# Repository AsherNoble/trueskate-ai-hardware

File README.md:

# trueskate-ai-hardware

Hand-control layer for TrueSkate-AI. Slots in where WebDriverAgent does for
the phones: the agent sends touch gestures, this repo makes a robotic finger
perform them.

Time-critical control (FOC, trajectory execution, safety) runs on a Teensy
4.1. The host sends commands and reads state back; it never runs a control
loop.

## Structure

```
firmware/   PlatformIO project, board teensy41
  src/        controller firmware, one Axis per finger
  bringup/    bench sketches kept for the record, unchanged
host/       Python package (uv), touch API + motor clients
  src/        trueskate_ai_hardware
  config/     hand.yaml
  tests/      mock-path tests, no hardware needed
docs/       wiring, pin map, bring-up notes, protocol draft
pcb/        through-hole six-axis carrier, KiCad source and review package
```

## Build the firmware

```sh
cd firmware && pio run
```

Does not flash. Add `-t upload` with the board connected.

## Run the host tests

```sh
cd host && uv sync --extra dev && uv run pytest
```

## Status

Firmware drives one axis and builds. The host is a skeleton: the touch API
mirrors the interface but does not move anything, and the serial protocol in
`docs/protocol.md` is a draft. `MockMotorClient` works with no hardware.

Start with [docs/bringup.md](docs/bringup.md) for what the bench has proved.

The [six-axis carrier review package](pcb/README.md) is a separate hardware
design, not yet released for fabrication. Its current edge layout uses six JLC-assembled JST connectors, hand-soldered THT parts,
and a hardware kill circuit. See [layout changes and outstanding checks](docs/pcb/edge-layout.md); start with the
[one-page net guide](docs/pcb/nets.md). Firmware still needs migration from the
one-axis bench pin assignments before use with this carrier.

## Licence

MIT. `orca_core` (MIT, ORCA) was studied as a reference for the motor-client
and serial-framing patterns; no code was copied.

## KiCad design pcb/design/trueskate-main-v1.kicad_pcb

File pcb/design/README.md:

# Current KiCad design

Open [trueskate-main-v1.kicad_pro](trueskate-main-v1.kicad_pro) in KiCad 10.
The project opens the PCB and its hierarchical schematic sheets. The local
symbol/footprint libraries and their tables live beside the project, so KiCad's
`${KIPRJMOD}` references remain relative and portable.

`data/` contains the declarative axis/pin mapping, nominal stackup, circuit data,
manual route records and placement baseline used by the scripts. `routing/`
contains the checked-in signal-routing session. See [tool commands](../scripts/README.md)
before rebuilding: regeneration overwrites the native design.

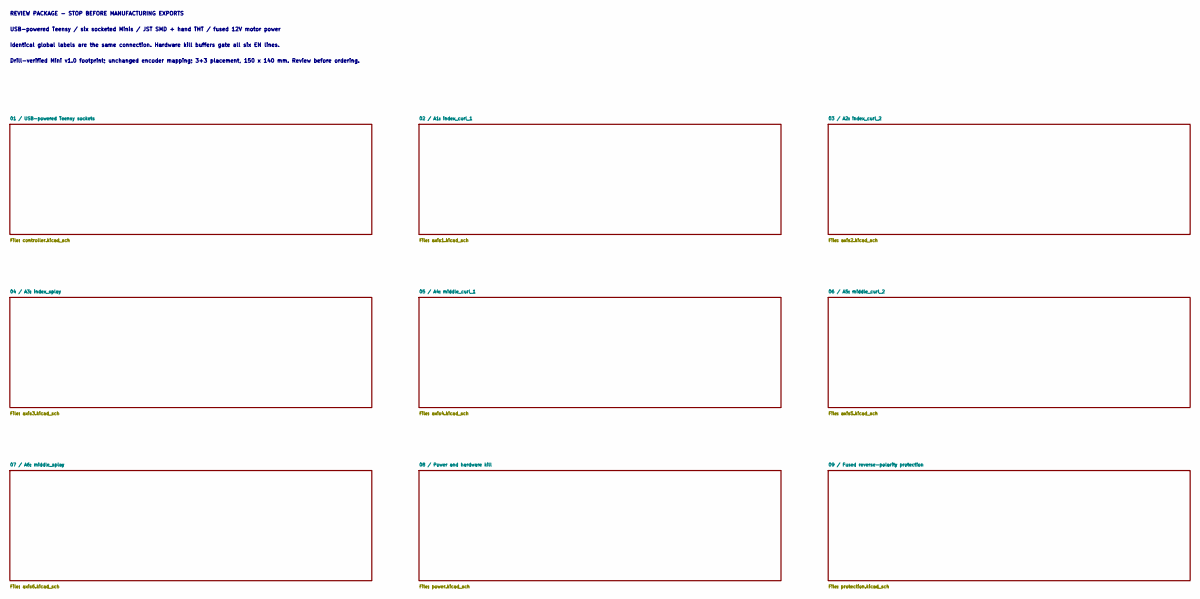
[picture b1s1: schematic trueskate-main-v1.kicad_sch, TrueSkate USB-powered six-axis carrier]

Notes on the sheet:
REVIEW PACKAGE - STOP BEFORE MANUFACTURING EXPORTS
USB-powered Teensy / six socketed Minis / JST SMD + hand THT / fused 12V motor power
Identical global labels are the same connection. Hardware kill buffers gate all six EN lines.
Drill-verified Mini v1.0 footprint; unchanged encoder mapping; 3+3 placement, 150 x 140 mm. Review before ordering.

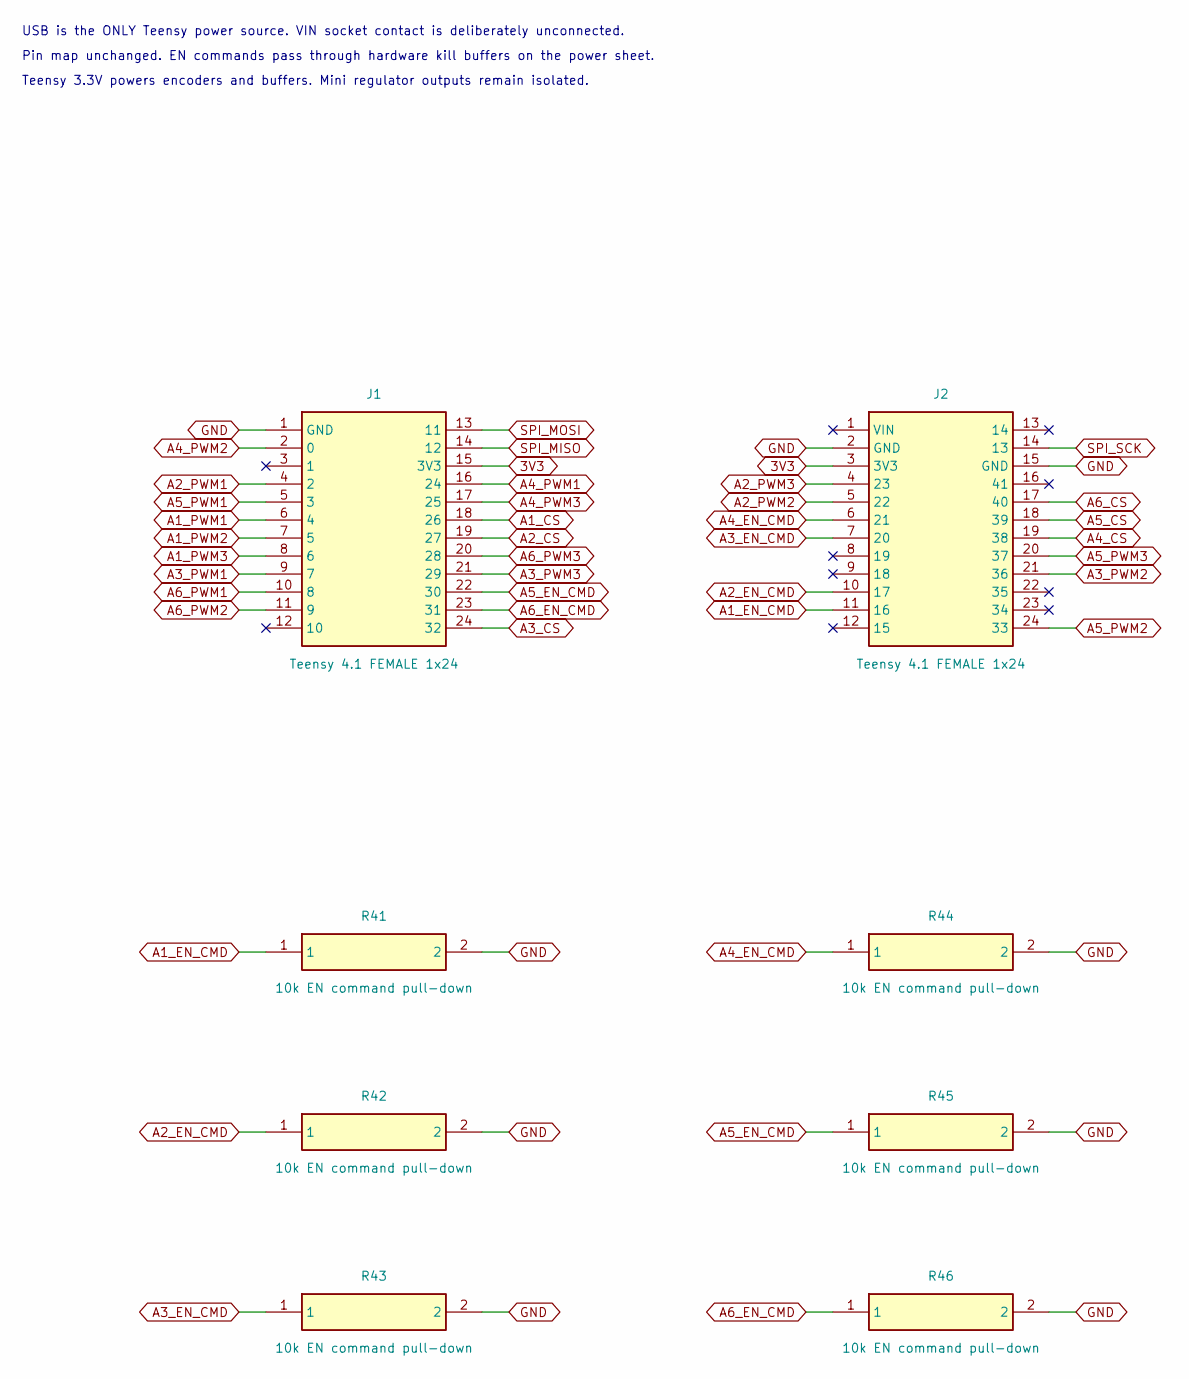
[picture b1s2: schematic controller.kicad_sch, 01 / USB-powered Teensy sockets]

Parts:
J1, J2: Teensy 4.1 FEMALE 1x24; Edge_PinSocket_1x24_P2.54mm_Vertical
R41, R42, R43, R44, R45, R46: 10k EN command pull-down; Edge_R_Axial_DIN0207_L6.3mm_D2.5mm_P7.62mm_Horizontal

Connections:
3V3: J1.15 (3V3), J2.3 (3V3); also elsewhere on the board
A1_CS: J1.18 (26); also elsewhere on the board
A1_EN_CMD: J2.11 (16), R41.1; also elsewhere on the board
A1_PWM1: J1.6 (4); also elsewhere on the board
A1_PWM2: J1.7 (5); also elsewhere on the board
A1_PWM3: J1.8 (6); also elsewhere on the board
A2_CS: J1.19 (27); also elsewhere on the board
A2_EN_CMD: J2.10 (17), R42.1; also elsewhere on the board
A2_PWM1: J1.4 (2); also elsewhere on the board
A2_PWM2: J2.5 (22); also elsewhere on the board
A2_PWM3: J2.4 (23); also elsewhere on the board
A3_CS: J1.24 (32); also elsewhere on the board
A3_EN_CMD: J2.7 (20), R43.1; also elsewhere on the board
A3_PWM1: J1.9 (7); also elsewhere on the board
A3_PWM2: J2.21 (36); also elsewhere on the board
A3_PWM3: J1.21 (29); also elsewhere on the board
A4_CS: J2.19 (38); also elsewhere on the board
A4_EN_CMD: J2.6 (21), R44.1; also elsewhere on the board
A4_PWM1: J1.16 (24); also elsewhere on the board
A4_PWM2: J1.2 (0); also elsewhere on the board
A4_PWM3: J1.17 (25); also elsewhere on the board
A5_CS: J2.18 (39); also elsewhere on the board
A5_EN_CMD: J1.22 (30), R45.1; also elsewhere on the board
A5_PWM1: J1.5 (3); also elsewhere on the board
A5_PWM2: J2.24 (33); also elsewhere on the board
A5_PWM3: J2.20 (37); also elsewhere on the board
A6_CS: J2.17 (40); also elsewhere on the board
A6_EN_CMD: J1.23 (31), R46.1; also elsewhere on the board
A6_PWM1: J1.10 (8); also elsewhere on the board
A6_PWM2: J1.11 (9); also elsewhere on the board
A6_PWM3: J1.20 (28); also elsewhere on the board
GND: J1.1 (GND), J2.2 (GND), J2.15 (GND), R41.2, R42.2, R43.2, R44.2, R45.2, R46.2; also elsewhere on the board
SPI_MISO: J1.14 (12); also elsewhere on the board
SPI_MOSI: J1.13 (11); also elsewhere on the board
SPI_SCK: J2.14 (13); also elsewhere on the board

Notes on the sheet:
USB is the ONLY Teensy power source. VIN socket contact is deliberately unconnected.
Pin map unchanged. EN commands pass through hardware kill buffers on the power sheet.
Teensy 3.3V powers encoders and buffers. Mini regulator outputs remain isolated.

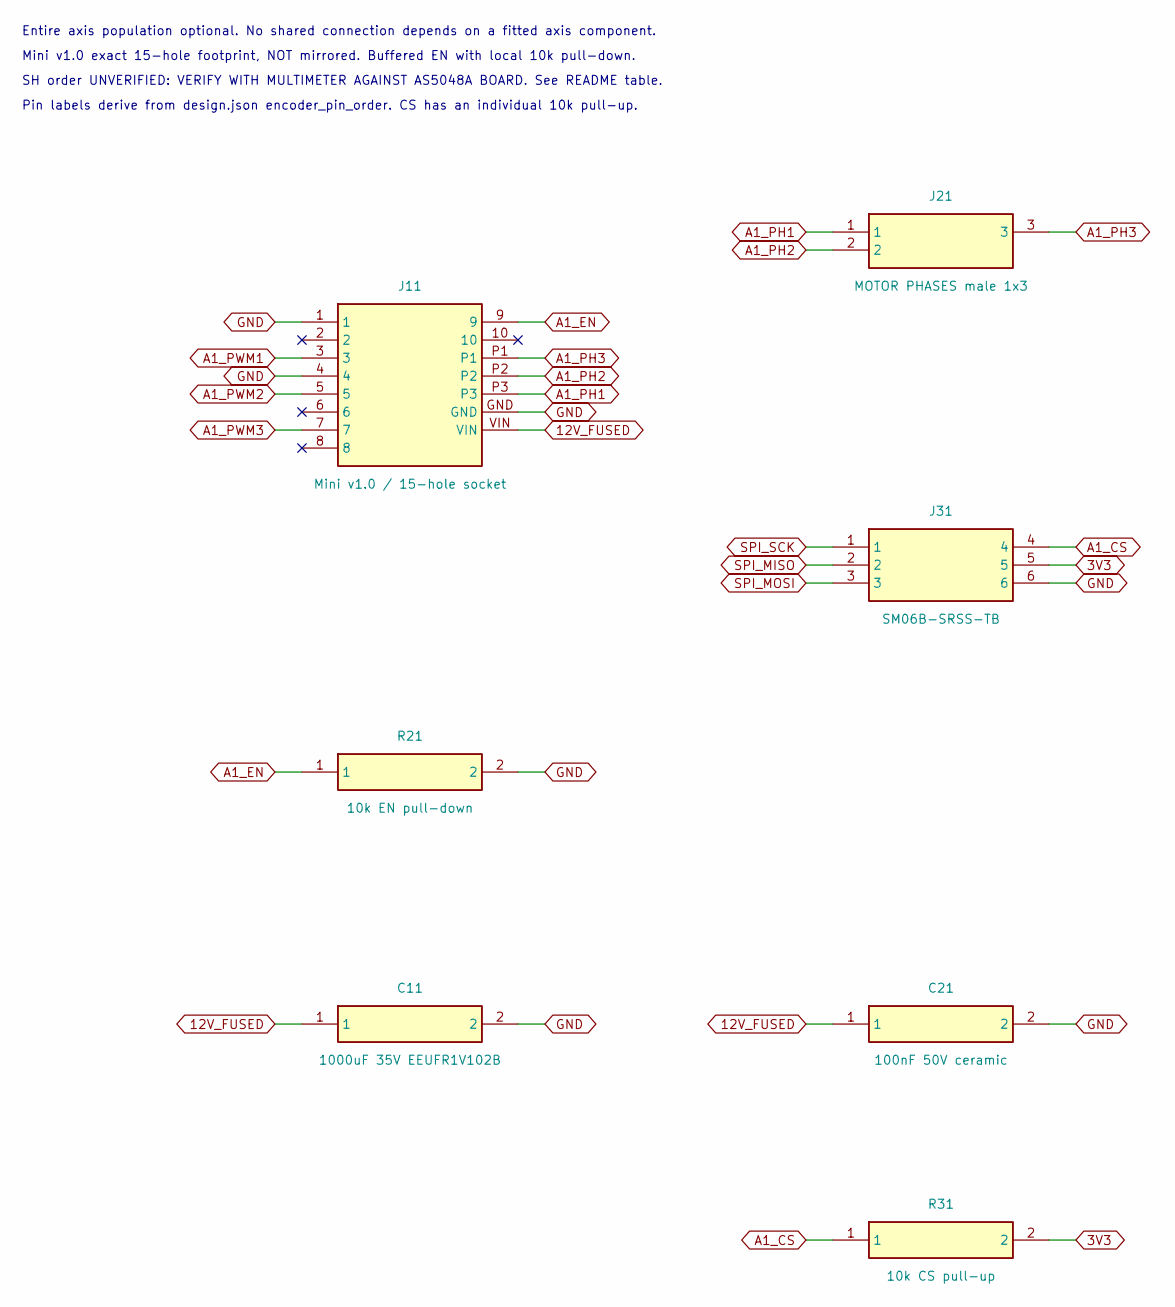
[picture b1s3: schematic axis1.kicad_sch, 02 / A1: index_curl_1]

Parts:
C11: 1000uF 35V EEUFR1V102B; Edge_CP_Radial_D12.5mm_P5.00mm
C21: 100nF 50V ceramic; Edge_C_Disc_D5.0mm_W2.5mm_P5.00mm
J11: Mini v1.0 / 15-hole socket; SimpleFOC_Mini_v1.0
J21: MOTOR PHASES male 1x3; Edge_PinHeader_1x03_P2.54mm_Vertical
J31: SM06B-SRSS-TB; Edge_JST_SH_SM06B-SRSS-TB_1x06-1MP_P1.00mm_Horizontal
R21: 10k EN pull-down; Edge_R_Axial_DIN0207_L6.3mm_D2.5mm_P7.62mm_Horizontal
R31: 10k CS pull-up; Edge_R_Axial_DIN0207_L6.3mm_D2.5mm_P7.62mm_Horizontal

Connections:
3V3: J31.5, R31.2; also elsewhere on the board
12V_FUSED: C11.1, C21.1, J11.VIN; also elsewhere on the board
A1_CS: J31.4, R31.1; also elsewhere on the board
A1_EN: J11.9, R21.1; also elsewhere on the board
A1_PH1: J11.P3, J21.1
A1_PH2: J11.P2, J21.2
A1_PH3: J11.P1, J21.3
A1_PWM1: J11.3; also elsewhere on the board
A1_PWM2: J11.5; also elsewhere on the board
A1_PWM3: J11.7; also elsewhere on the board
GND: C11.2, C21.2, J11.1, J11.4, J11.GND, J31.6, R21.2; also elsewhere on the board
SPI_MISO: J31.2; also elsewhere on the board
SPI_MOSI: J31.3; also elsewhere on the board
SPI_SCK: J31.1; also elsewhere on the board

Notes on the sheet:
Entire axis population optional. No shared connection depends on a fitted axis component.
Mini v1.0 exact 15-hole footprint, NOT mirrored. Buffered EN with local 10k pull-down.
SH order UNVERIFIED: VERIFY WITH MULTIMETER AGAINST AS5048A BOARD. See README table.
Pin labels derive from design.json encoder_pin_order. CS has an individual 10k pull-up.

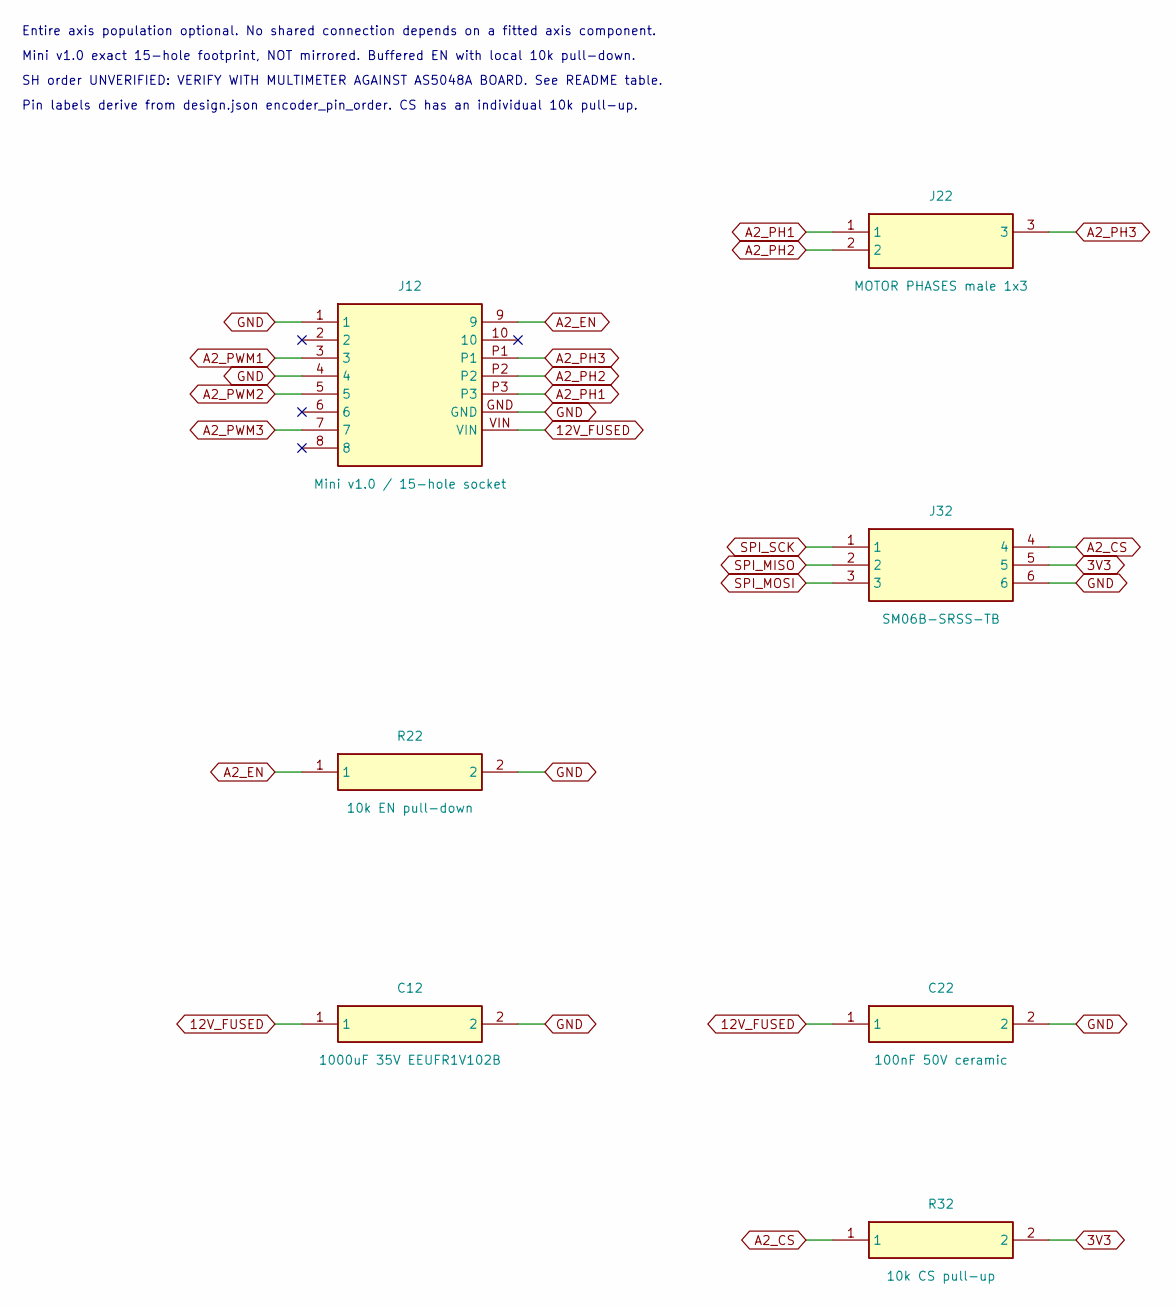
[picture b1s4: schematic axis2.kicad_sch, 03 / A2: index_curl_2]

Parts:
C12: 1000uF 35V EEUFR1V102B; Edge_CP_Radial_D12.5mm_P5.00mm
C22: 100nF 50V ceramic; Edge_C_Disc_D5.0mm_W2.5mm_P5.00mm
J12: Mini v1.0 / 15-hole socket; SimpleFOC_Mini_v1.0
J22: MOTOR PHASES male 1x3; Edge_PinHeader_1x03_P2.54mm_Vertical
J32: SM06B-SRSS-TB; Edge_JST_SH_SM06B-SRSS-TB_1x06-1MP_P1.00mm_Horizontal
R22: 10k EN pull-down; Edge_R_Axial_DIN0207_L6.3mm_D2.5mm_P7.62mm_Horizontal
R32: 10k CS pull-up; Edge_R_Axial_DIN0207_L6.3mm_D2.5mm_P7.62mm_Horizontal

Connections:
3V3: J32.5, R32.2; also elsewhere on the board
12V_FUSED: C12.1, C22.1, J12.VIN; also elsewhere on the board
A2_CS: J32.4, R32.1; also elsewhere on the board
A2_EN: J12.9, R22.1; also elsewhere on the board
A2_PH1: J12.P3, J22.1
A2_PH2: J12.P2, J22.2
A2_PH3: J12.P1, J22.3
A2_PWM1: J12.3; also elsewhere on the board
A2_PWM2: J12.5; also elsewhere on the board
A2_PWM3: J12.7; also elsewhere on the board
GND: C12.2, C22.2, J12.1, J12.4, J12.GND, J32.6, R22.2; also elsewhere on the board
SPI_MISO: J32.2; also elsewhere on the board
SPI_MOSI: J32.3; also elsewhere on the board
SPI_SCK: J32.1; also elsewhere on the board

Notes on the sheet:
Entire axis population optional. No shared connection depends on a fitted axis component.
Mini v1.0 exact 15-hole footprint, NOT mirrored. Buffered EN with local 10k pull-down.
SH order UNVERIFIED: VERIFY WITH MULTIMETER AGAINST AS5048A BOARD. See README table.
Pin labels derive from design.json encoder_pin_order. CS has an individual 10k pull-up.

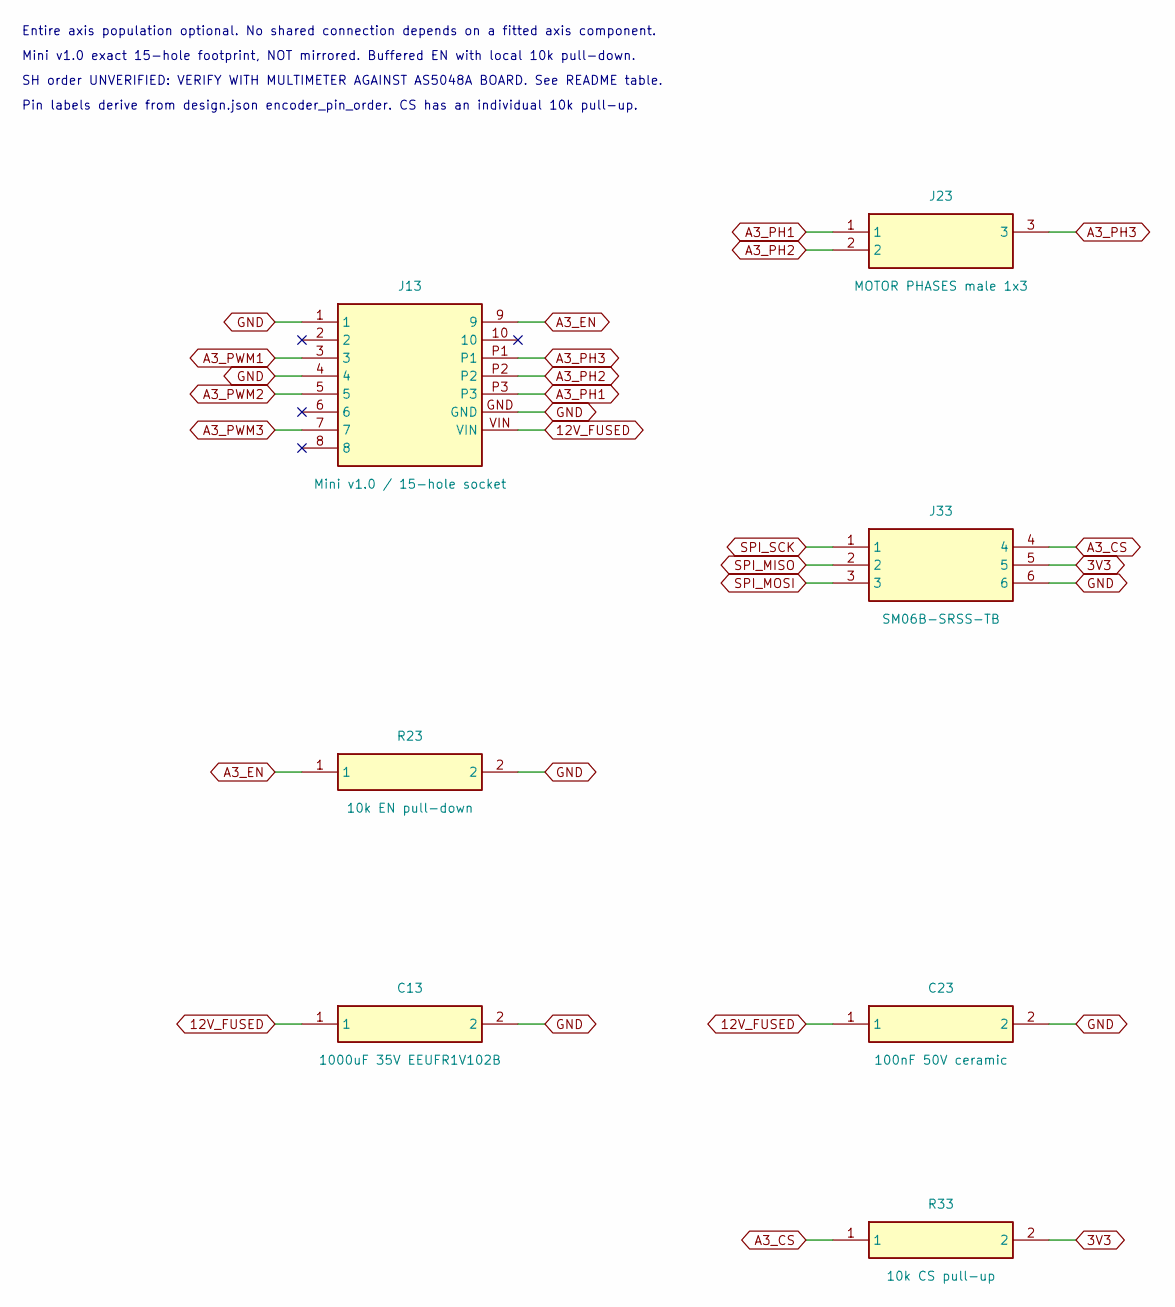
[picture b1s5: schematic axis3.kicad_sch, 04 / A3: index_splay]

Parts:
C13: 1000uF 35V EEUFR1V102B; Edge_CP_Radial_D12.5mm_P5.00mm
C23: 100nF 50V ceramic; Edge_C_Disc_D5.0mm_W2.5mm_P5.00mm
J13: Mini v1.0 / 15-hole socket; SimpleFOC_Mini_v1.0
J23: MOTOR PHASES male 1x3; Edge_PinHeader_1x03_P2.54mm_Vertical
J33: SM06B-SRSS-TB; Edge_JST_SH_SM06B-SRSS-TB_1x06-1MP_P1.00mm_Horizontal
R23: 10k EN pull-down; Edge_R_Axial_DIN0207_L6.3mm_D2.5mm_P7.62mm_Horizontal
R33: 10k CS pull-up; Edge_R_Axial_DIN0207_L6.3mm_D2.5mm_P7.62mm_Horizontal

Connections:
3V3: J33.5, R33.2; also elsewhere on the board
12V_FUSED: C13.1, C23.1, J13.VIN; also elsewhere on the board
A3_CS: J33.4, R33.1; also elsewhere on the board
A3_EN: J13.9, R23.1; also elsewhere on the board
A3_PH1: J13.P3, J23.1
A3_PH2: J13.P2, J23.2
A3_PH3: J13.P1, J23.3
A3_PWM1: J13.3; also elsewhere on the board
A3_PWM2: J13.5; also elsewhere on the board
A3_PWM3: J13.7; also elsewhere on the board
GND: C13.2, C23.2, J13.1, J13.4, J13.GND, J33.6, R23.2; also elsewhere on the board
SPI_MISO: J33.2; also elsewhere on the board
SPI_MOSI: J33.3; also elsewhere on the board
SPI_SCK: J33.1; also elsewhere on the board

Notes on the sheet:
Entire axis population optional. No shared connection depends on a fitted axis component.
Mini v1.0 exact 15-hole footprint, NOT mirrored. Buffered EN with local 10k pull-down.
SH order UNVERIFIED: VERIFY WITH MULTIMETER AGAINST AS5048A BOARD. See README table.
Pin labels derive from design.json encoder_pin_order. CS has an individual 10k pull-up.

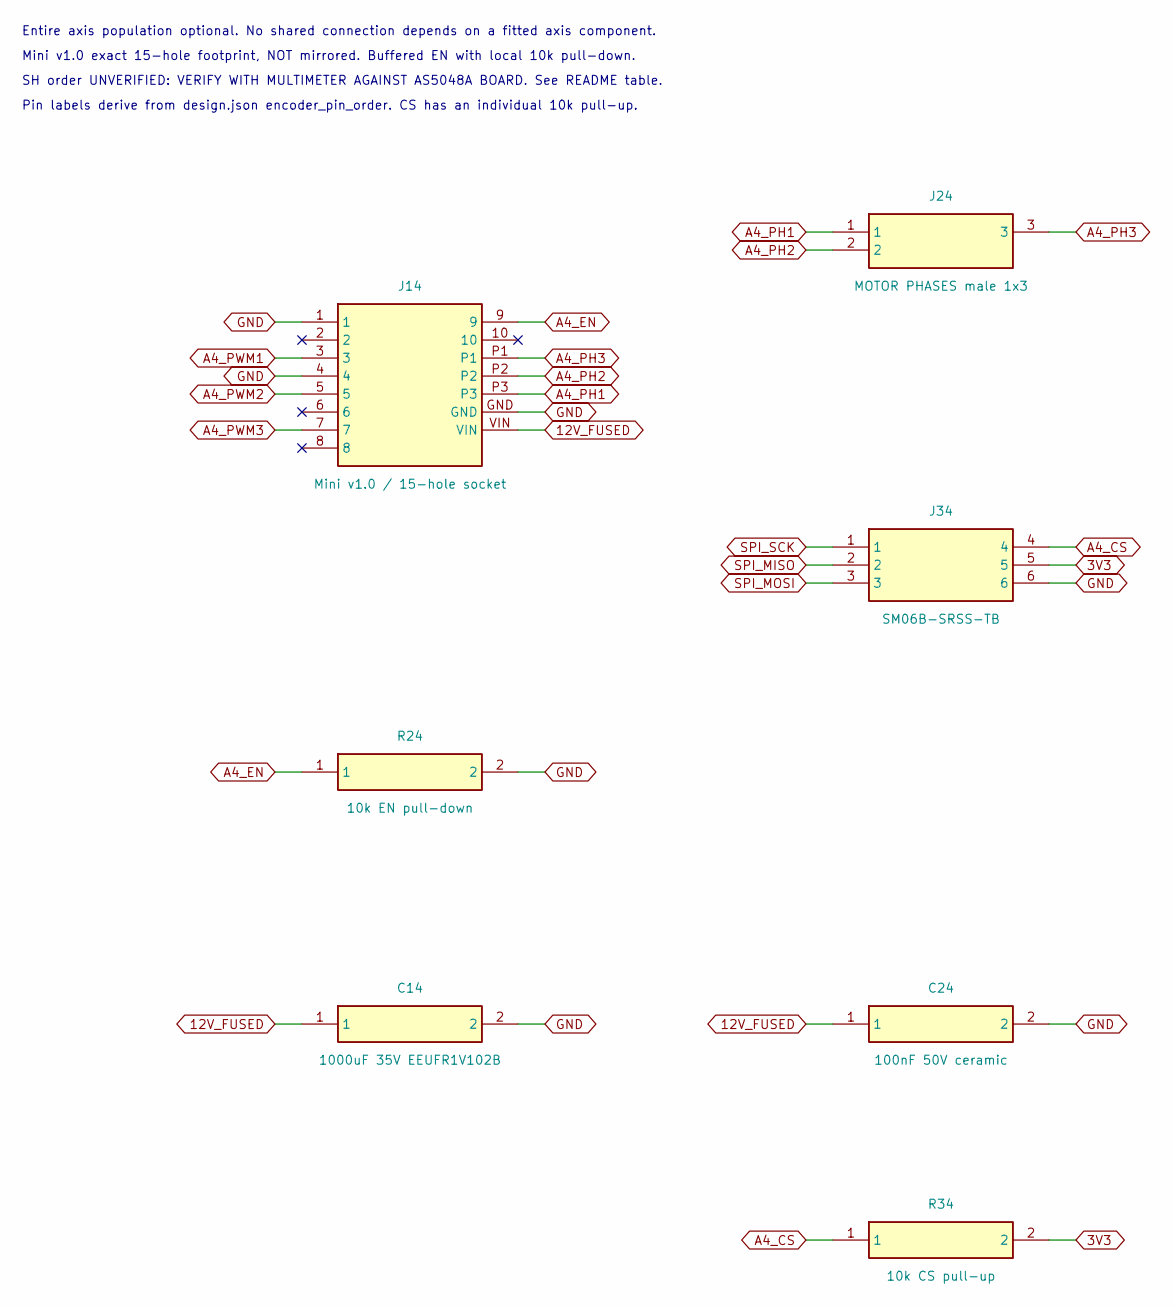
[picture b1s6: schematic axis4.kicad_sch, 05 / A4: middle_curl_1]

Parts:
C14: 1000uF 35V EEUFR1V102B; Edge_CP_Radial_D12.5mm_P5.00mm
C24: 100nF 50V ceramic; Edge_C_Disc_D5.0mm_W2.5mm_P5.00mm
J14: Mini v1.0 / 15-hole socket; SimpleFOC_Mini_v1.0
J24: MOTOR PHASES male 1x3; Edge_PinHeader_1x03_P2.54mm_Vertical
J34: SM06B-SRSS-TB; Edge_JST_SH_SM06B-SRSS-TB_1x06-1MP_P1.00mm_Horizontal
R24: 10k EN pull-down; Edge_R_Axial_DIN0207_L6.3mm_D2.5mm_P7.62mm_Horizontal
R34: 10k CS pull-up; Edge_R_Axial_DIN0207_L6.3mm_D2.5mm_P7.62mm_Horizontal

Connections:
3V3: J34.5, R34.2; also elsewhere on the board
12V_FUSED: C14.1, C24.1, J14.VIN; also elsewhere on the board
A4_CS: J34.4, R34.1; also elsewhere on the board
A4_EN: J14.9, R24.1; also elsewhere on the board
A4_PH1: J14.P3, J24.1
A4_PH2: J14.P2, J24.2
A4_PH3: J14.P1, J24.3
A4_PWM1: J14.3; also elsewhere on the board
A4_PWM2: J14.5; also elsewhere on the board
A4_PWM3: J14.7; also elsewhere on the board
GND: C14.2, C24.2, J14.1, J14.4, J14.GND, J34.6, R24.2; also elsewhere on the board
SPI_MISO: J34.2; also elsewhere on the board
SPI_MOSI: J34.3; also elsewhere on the board
SPI_SCK: J34.1; also elsewhere on the board

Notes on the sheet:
Entire axis population optional. No shared connection depends on a fitted axis component.
Mini v1.0 exact 15-hole footprint, NOT mirrored. Buffered EN with local 10k pull-down.
SH order UNVERIFIED: VERIFY WITH MULTIMETER AGAINST AS5048A BOARD. See README table.
Pin labels derive from design.json encoder_pin_order. CS has an individual 10k pull-up.

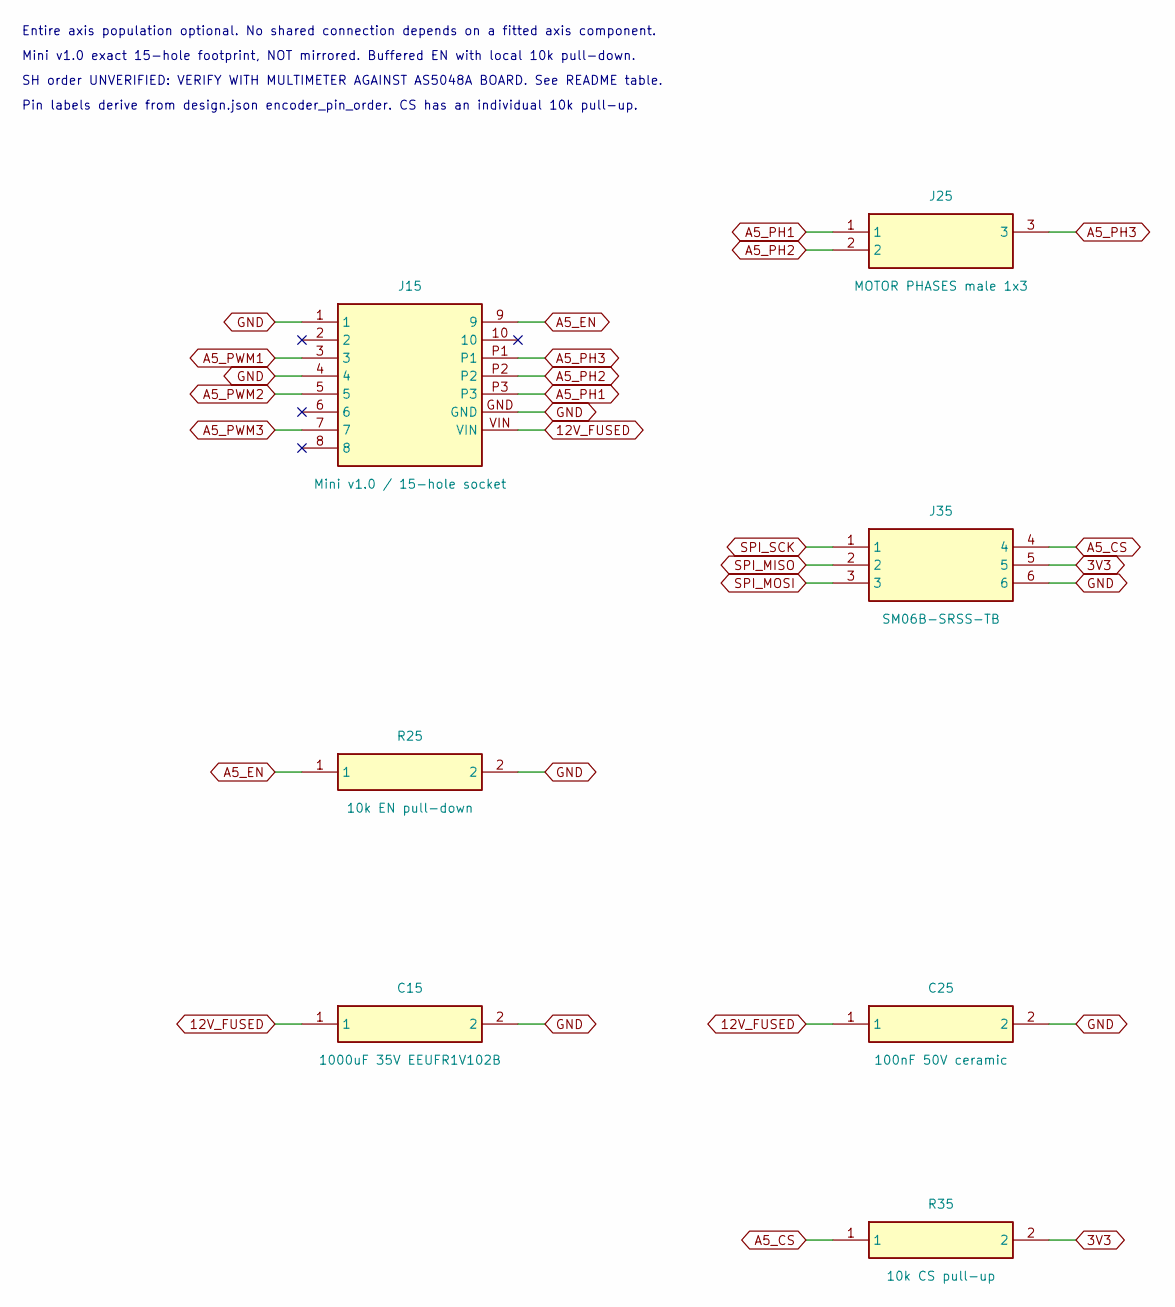
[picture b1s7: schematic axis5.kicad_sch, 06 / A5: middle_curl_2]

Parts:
C15: 1000uF 35V EEUFR1V102B; Edge_CP_Radial_D12.5mm_P5.00mm
C25: 100nF 50V ceramic; Edge_C_Disc_D5.0mm_W2.5mm_P5.00mm
J15: Mini v1.0 / 15-hole socket; SimpleFOC_Mini_v1.0
J25: MOTOR PHASES male 1x3; Edge_PinHeader_1x03_P2.54mm_Vertical
J35: SM06B-SRSS-TB; Edge_JST_SH_SM06B-SRSS-TB_1x06-1MP_P1.00mm_Horizontal
R25: 10k EN pull-down; Edge_R_Axial_DIN0207_L6.3mm_D2.5mm_P7.62mm_Horizontal
R35: 10k CS pull-up; Edge_R_Axial_DIN0207_L6.3mm_D2.5mm_P7.62mm_Horizontal

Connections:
3V3: J35.5, R35.2; also elsewhere on the board
12V_FUSED: C15.1, C25.1, J15.VIN; also elsewhere on the board
A5_CS: J35.4, R35.1; also elsewhere on the board
A5_EN: J15.9, R25.1; also elsewhere on the board
A5_PH1: J15.P3, J25.1
A5_PH2: J15.P2, J25.2
A5_PH3: J15.P1, J25.3
A5_PWM1: J15.3; also elsewhere on the board
A5_PWM2: J15.5; also elsewhere on the board
A5_PWM3: J15.7; also elsewhere on the board
GND: C15.2, C25.2, J15.1, J15.4, J15.GND, J35.6, R25.2; also elsewhere on the board
SPI_MISO: J35.2; also elsewhere on the board
SPI_MOSI: J35.3; also elsewhere on the board
SPI_SCK: J35.1; also elsewhere on the board

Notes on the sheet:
Entire axis population optional. No shared connection depends on a fitted axis component.
Mini v1.0 exact 15-hole footprint, NOT mirrored. Buffered EN with local 10k pull-down.
SH order UNVERIFIED: VERIFY WITH MULTIMETER AGAINST AS5048A BOARD. See README table.
Pin labels derive from design.json encoder_pin_order. CS has an individual 10k pull-up.

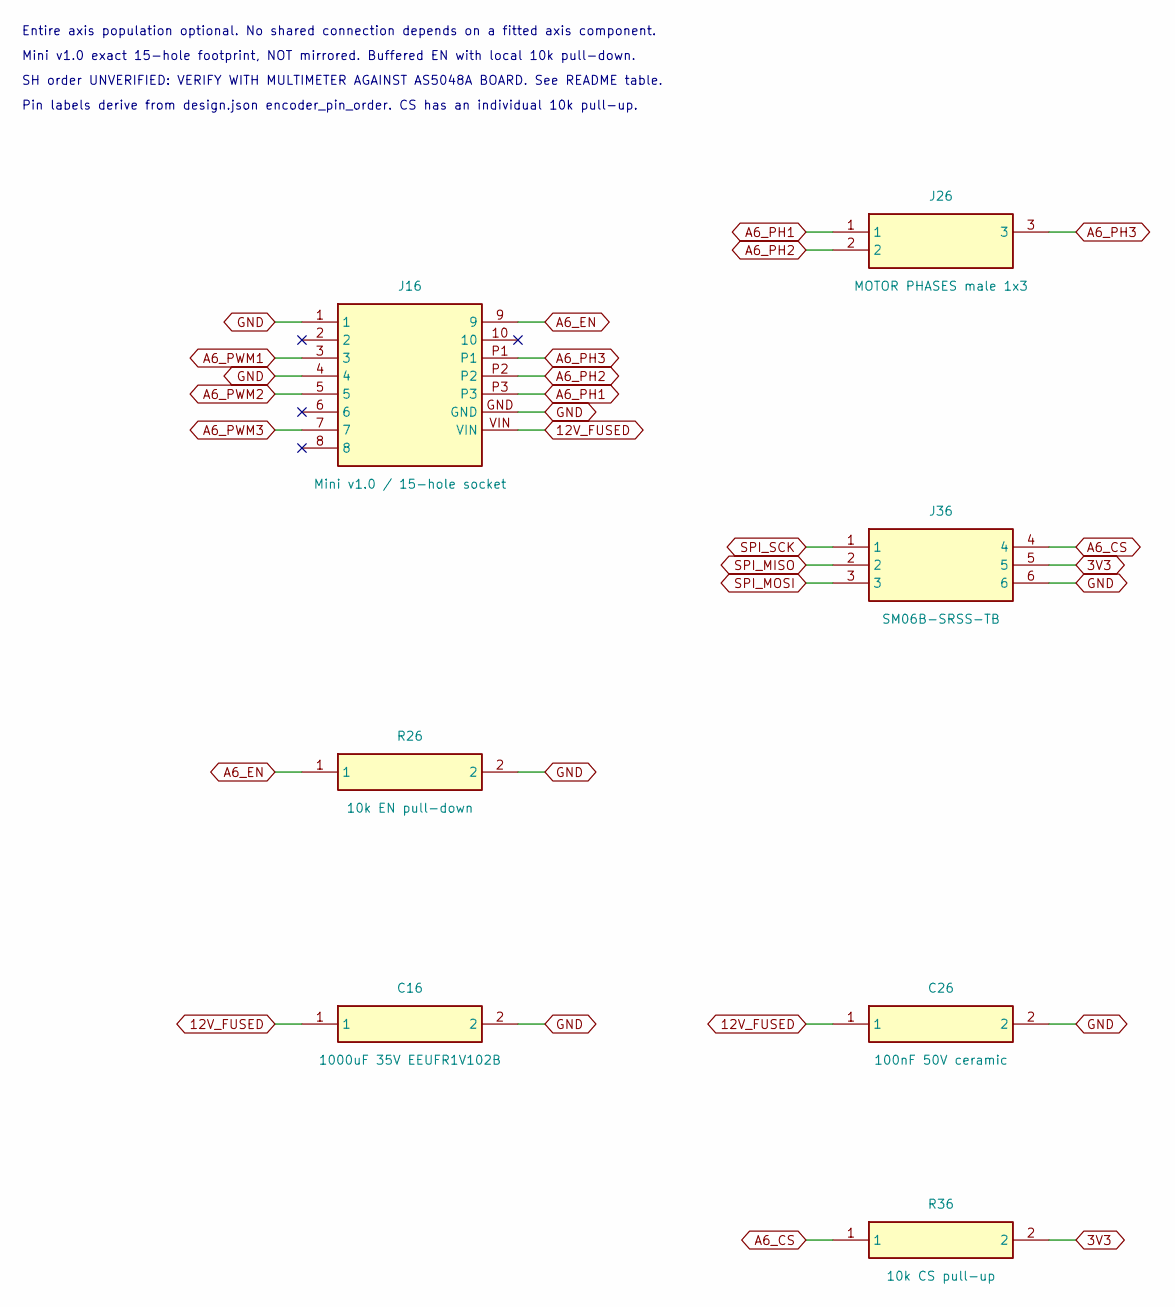
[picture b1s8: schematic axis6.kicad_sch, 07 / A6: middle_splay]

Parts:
C16: 1000uF 35V EEUFR1V102B; Edge_CP_Radial_D12.5mm_P5.00mm
C26: 100nF 50V ceramic; Edge_C_Disc_D5.0mm_W2.5mm_P5.00mm
J16: Mini v1.0 / 15-hole socket; SimpleFOC_Mini_v1.0
J26: MOTOR PHASES male 1x3; Edge_PinHeader_1x03_P2.54mm_Vertical
J36: SM06B-SRSS-TB; Edge_JST_SH_SM06B-SRSS-TB_1x06-1MP_P1.00mm_Horizontal
R26: 10k EN pull-down; Edge_R_Axial_DIN0207_L6.3mm_D2.5mm_P7.62mm_Horizontal
R36: 10k CS pull-up; Edge_R_Axial_DIN0207_L6.3mm_D2.5mm_P7.62mm_Horizontal

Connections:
3V3: J36.5, R36.2; also elsewhere on the board
12V_FUSED: C16.1, C26.1, J16.VIN; also elsewhere on the board
A6_CS: J36.4, R36.1; also elsewhere on the board
A6_EN: J16.9, R26.1; also elsewhere on the board
A6_PH1: J16.P3, J26.1
A6_PH2: J16.P2, J26.2
A6_PH3: J16.P1, J26.3
A6_PWM1: J16.3; also elsewhere on the board
A6_PWM2: J16.5; also elsewhere on the board
A6_PWM3: J16.7; also elsewhere on the board
GND: C16.2, C26.2, J16.1, J16.4, J16.GND, J36.6, R26.2; also elsewhere on the board
SPI_MISO: J36.2; also elsewhere on the board
SPI_MOSI: J36.3; also elsewhere on the board
SPI_SCK: J36.1; also elsewhere on the board

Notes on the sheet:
Entire axis population optional. No shared connection depends on a fitted axis component.
Mini v1.0 exact 15-hole footprint, NOT mirrored. Buffered EN with local 10k pull-down.
SH order UNVERIFIED: VERIFY WITH MULTIMETER AGAINST AS5048A BOARD. See README table.
Pin labels derive from design.json encoder_pin_order. CS has an individual 10k pull-up.

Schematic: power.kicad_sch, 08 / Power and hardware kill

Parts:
C1, C2: 100nF buffer bypass; Edge_C_Disc_D5.0mm_W2.5mm_P5.00mm
F1: Keystone 3557-2 ATO holder; Keystone_3557-2_ATO
J5: 12V INPUT + / -; Edge_TerminalBlock_Phoenix_MKDS-1,5-2-5.08_1x02_P5.08mm_Hor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
J6: NC KILL SWITCH; Edge_PinHeader_1x02_P2.54mm_Vertical
R1: 10k /OE pull-up; Edge_R_Axial_DIN0207_L6.3mm_D2.5mm_P7.62mm_Horizontal
U1, U2: SN74HC125N; Edge_DIP-14_W7.62mm

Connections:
3V3: C1.1, C2.1, R1.2, U1.13 (/4OE), U1.14 (VCC), U2.13 (/4OE), U2.14 (VCC); also elsewhere on the board
12V_IN: F1.1, J5.1
12V_PREPOL: F1.2; also elsewhere on the board
A1_EN: U1.3 (1Y); also elsewhere on the board
A1_EN_CMD: U1.2 (1A); also elsewhere on the board
A2_EN: U1.6 (2Y); also elsewhere on the board
A2_EN_CMD: U1.5 (2A); also elsewhere on the board
A3_EN: U1.8 (3Y); also elsewhere on the board
A3_EN_CMD: U1.9 (3A); also elsewhere on the board
A4_EN: U2.3 (1Y); also elsewhere on the board
A4_EN_CMD: U2.2 (1A); also elsewhere on the board
A5_EN: U2.6 (2Y); also elsewhere on the board
A5_EN_CMD: U2.5 (2A); also elsewhere on the board
A6_EN: U2.8 (3Y); also elsewhere on the board
A6_EN_CMD: U2.9 (3A); also elsewhere on the board
EN_DISABLE: J6.1, R1.1, U1.1 (/1OE), U1.4 (/2OE), U1.10 (/3OE), U2.1 (/1OE), U2.4 (/2OE), U2.10 (/3OE)
GND: C1.2, C2.2, J5.2, J6.2, U1.7 (GND), U1.12 (4A), U2.7 (GND), U2.12 (4A); also elsewhere on the board

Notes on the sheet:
12V motor rail only. 12mm shared bus; 2mm per-axis feeds; 1oz copper. Thermal evaluation stopped.
NC switch across J6: closed permits EN commands, open tri-states every EN output.
R1 pulls /OE high on open loop. Local R21-R26 pull EN low independently of firmware.
Reclosing switch restores commanded state; no restart latch. Kill does NOT isolate 12V.
U1/U2 SN74HC125N PDIP14, 3.3V, no Ioff. Unused inputs tied; unused outputs NC.

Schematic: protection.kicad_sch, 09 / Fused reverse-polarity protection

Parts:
D1: 1N4742A 12V; Edge_D_DO-41_SOD81_P10.16mm_Horizontal
Q1: IRF4905PBF; Edge_TO-220-3_Vertical
R2: 10k gate pull-down; Edge_R_Axial_DIN0207_L6.3mm_D2.5mm_P7.62mm_Horizontal

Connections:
12V_FUSED: D1.1 (K / source), Q1.3 (S); also elsewhere on the board
12V_PREPOL: Q1.2 (D / tab); also elsewhere on the board
GND: R2.2; also elsewhere on the board
POL_GATE: D1.2 (A / gate), Q1.1 (G), R2.1

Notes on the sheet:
F1 -> Q1 drain; Q1 source -> protected 12V_FUSED bus. P-MOS body diode points input to load.
D1 cathode (band/pad1) to source; anode to gate. R2 10k from gate to GND.
IRF4905PbF: -55V, 20mOhm max at VGS=-10V, -74A case rating. TO-220 pin1 G,2 D/tab,3 S.
At 12A: 2.88W at 20mOhm, more when hot. Heat sink / assembly thermal verification required.
Single MOSFET is reverse-input protection, not reverse-current or load-disconnect protection.

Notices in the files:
pcb/design/trueskate-main-v1.kicad_pcb:
Asher Noble · CC BY-NC
